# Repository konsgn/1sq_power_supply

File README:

# 1 Square Power Supply

A Square inch power supply based on parts from a LM2596 DC-DC buck 
module. Uses an additional Quad-op-amp and STM32F030 to control the 
requlation and display data to the oled screen.

## Big Ticket Components

* MCP6L94 - Quad Op Amp
* SSD1306 - 128*64 oled screen
* LM2596S - Buck Voltage regulator
* STM32F030F4 - Microcontroller
* L78L05 - 5V regulator 
* AP2210N - 3V3 regulator

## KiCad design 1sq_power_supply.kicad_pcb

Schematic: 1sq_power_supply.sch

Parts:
C2, C3, C5, C7, C8: C_Small
C4: 4.7u
C6, C9, C10: 1u
C11, C12, C13, C14, C17: 2u2
C15: DNP
C16: 10u
D1: SK54B
D2: M4
D3: D_Small
J1: TC2030-MCP; Homebrew_TC2030-MCP
J2, J3, J4, J5: Conn_01x02
J6: Conn_01x05_Male
L1: 33uH
OLEDM1: SSD1306
R1: 8200
R2: 470
R3: 750
R4, R5, R6, R7, R8, R11: R_Small
R9, R10: 1k5
R12: 10k
R13: 330
R14: .05
U1: L78L05_SOT89; SOT-89-3
U2: LM2596S-ADJ; TO-263-5_TabPin3
U3: STM32F030F4Px; TSSOP-20_4.4x6.5mm_P0.65mm
U4: AP2210N-3.3; SOT-23
U5: MCP6L94

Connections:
3.3v: C3.1, C5.1, C7.1, C12.2, C14.2, J1.1, J6.1, OLEDM1.6, OLEDM1.9, OLEDM1.11, U3.5, U3.16, U4.2 (VO)
5v: C4.1, C6.1, U1.1 (OUT), U4.3 (VI), U5.4 (V+)
/A_Limit: R10.2, U3.13
/A_Sense: C15.1, R11.2, U3.10, U5.1, U5.5 (+)
/Aset: C10.1, R10.1, U5.6 (-)
/BTN: J6.2, U3.8
/FB: D3.1, R1.2, R2.2, R3.1, U2.4 (FB)
/GNDout: J5.1, J5.2, R14.1, U5.3 (+)
/LCDRST: OLEDM1.14, U3.3
/PotSense: J6.4, U3.11
/RX: J6.3, U3.9
/SCL: OLEDM1.18, U3.17
/SDA: OLEDM1.19, OLEDM1.20, U3.18
/SWC: J1.4, U3.20
/SWD: J1.2, U3.19
/V_Target: R9.2, U3.12
/Vctrl: R3.2, U5.8, U5.9 (-)
/Vi_Sense: R4.1, R5.2, U3.7
/Vo_Sense: R6.1, R7.2, U3.6
/Vset: C9.1, R9.1, U5.10 (+)
/~RST: J1.3, U3.4
GND: C2.2, C3.2, C4.2, C5.2, C6.2, C7.2, C8.2, C9.2, C10.2, C12.1, C14.1, C16.2, C17.2, D1.2, D2.2, J1.5, J3.1, J3.2, J6.5, OLEDM1.1, OLEDM1.8, OLEDM1.10, OLEDM1.12, OLEDM1.13, OLEDM1.15, OLEDM1.16, OLEDM1.17, OLEDM1.21, OLEDM1.22, OLEDM1.23, OLEDM1.24, OLEDM1.25, OLEDM1.29, OLEDM1.30, R2.1, R5.1, R7.1, R8.2, R12.1, R13.2, R14.2, U1.2 (GND), U2.3 (GND), U3.15, U4.1 (GND), U5.11 (V-)
unnamed: C11.1, OLEDM1.3
unnamed: C11.2, OLEDM1.2
unnamed: C13.1, OLEDM1.5
unnamed: C13.2, OLEDM1.4
unnamed: C15.2, R8.1, R11.1, U5.2 (-)
unnamed: C16.1, OLEDM1.28
unnamed: C17.1, OLEDM1.27
unnamed: D1.1, L1.2, U2.2 (OUT)
unnamed: D3.2, U5.7
unnamed: OLEDM1.26, R13.1
unnamed: R12.2, U3.1
Vin: C2.1, D2.1, J2.1, J2.2, R4.2, U1.3 (IN), U2.1 (VIN), U2.5 (~ON~/OFF)
Vout: C8.1, J4.1, J4.2, L1.1, R1.1, R6.2

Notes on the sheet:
Aboost
Acomp
TIM3_CH1
TIM3_CH2
VBuffer

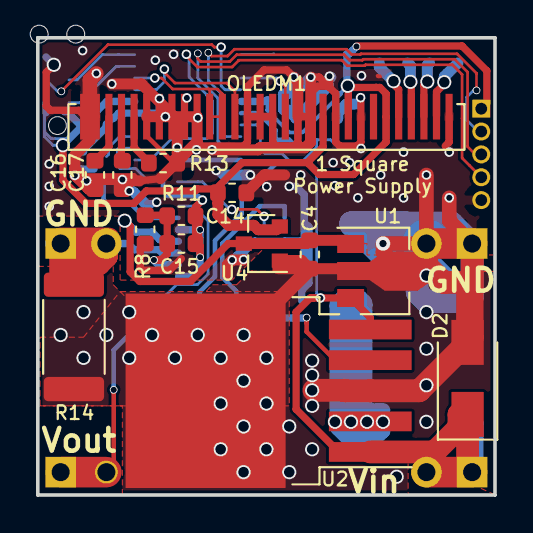
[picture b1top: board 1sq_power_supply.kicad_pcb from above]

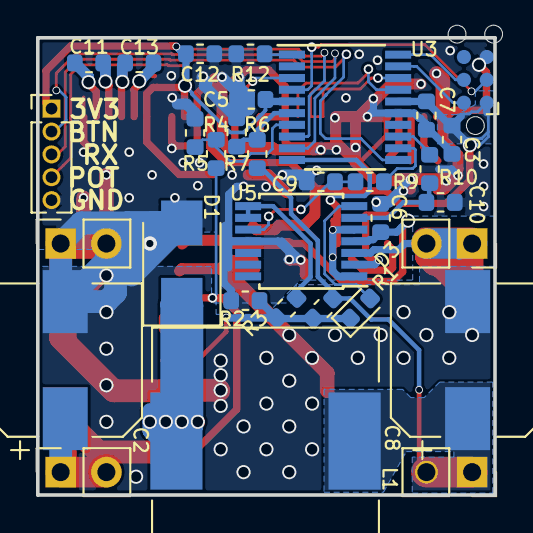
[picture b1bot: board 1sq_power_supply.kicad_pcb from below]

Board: 2 copper layers, 25.4 x 25.4 mm, 46 parts (32 on the bottom side), 35 nets.

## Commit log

2018-09-30 First Commit -v0.1
2018-09-30 Rename README to README.md
2018-10-03 added footprints
2019-02-22 2-22-19 update
